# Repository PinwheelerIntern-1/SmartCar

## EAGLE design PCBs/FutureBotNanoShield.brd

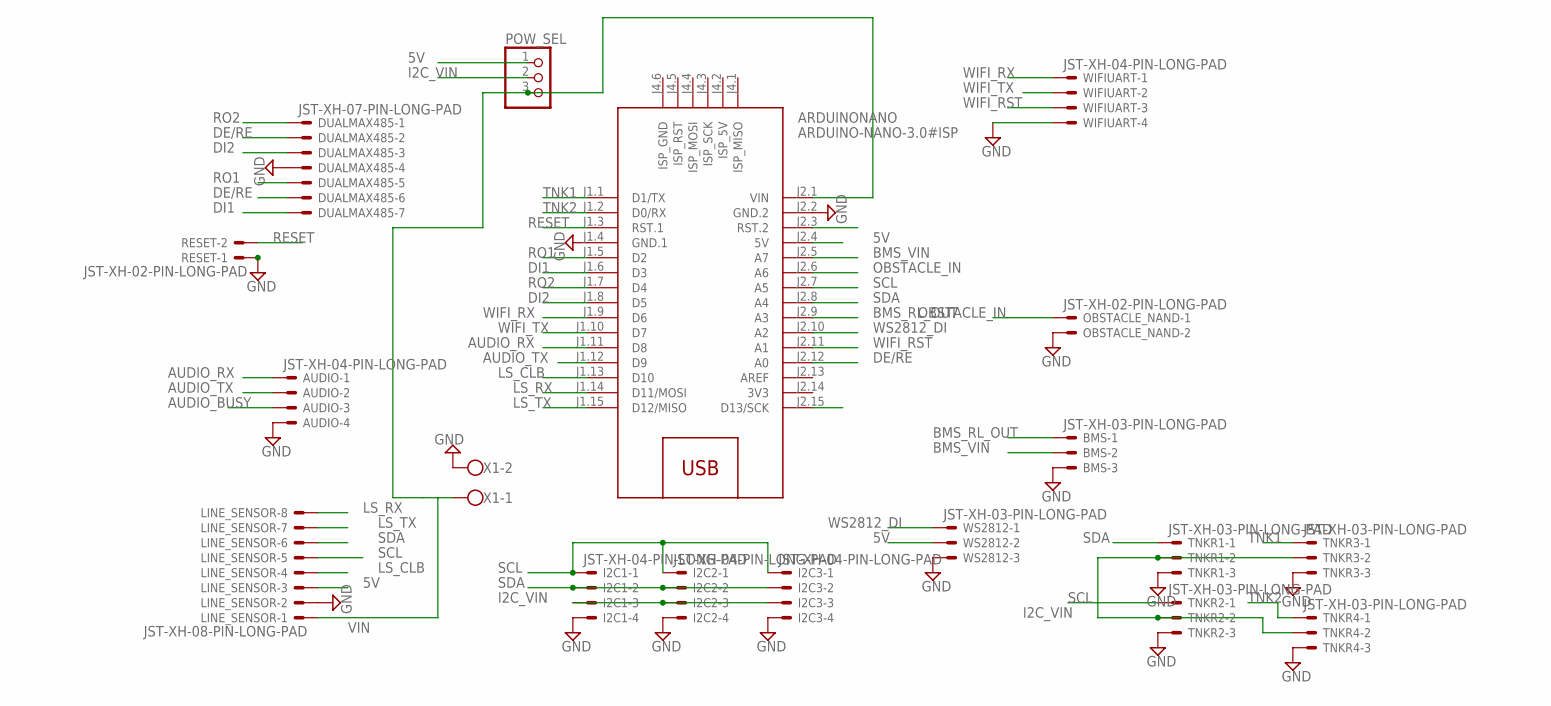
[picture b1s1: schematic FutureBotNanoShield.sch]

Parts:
ARDUINONANO: ARDUINO-NANO-3.0#ISP
AUDIO: JST-XH-04-PIN-LONG-PAD; JST-XH-04-PACKAGE-LONG-PAD
BMS: JST-XH-03-PIN-LONG-PAD; JST-XH-03-PACKAGE-LONG-PAD
DUALMAX485: JST-XH-07-PIN-LONG-PAD; JST-XH-07-PACKAGE-LONG-PAD
I2C1, I2C2, I2C3: JST-XH-04-PIN-LONG-PAD; JST-XH-04-PACKAGE-LONG-PAD
LINE_SENSOR: JST-XH-08-PIN-LONG-PAD; JST-XH-08-PACKAGE-LONG-PAD
OBSTACLE_NAND: JST-XH-02-PIN-LONG-PAD; JST-XH-02-PACKAGE-LONG-PAD
POW_SEL: PINHD-1X3; 1X03
RESET: JST-XH-02-PIN-LONG-PAD; JST-XH-02-PACKAGE-LONG-PAD
TNKR1, TNKR2, TNKR3, TNKR4: JST-XH-03-PIN-LONG-PAD; JST-XH-03-PACKAGE-LONG-PAD
WIFIUART: JST-XH-04-PIN-LONG-PAD; JST-XH-04-PACKAGE-LONG-PAD
WS2812: JST-XH-03-PIN-LONG-PAD; JST-XH-03-PACKAGE-LONG-PAD
X1: W237-102

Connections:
3V3: ARDUINONANO.J2.14 (3V3)
5V: ARDUINONANO.J2.4 (5V), LINE_SENSOR.3, POW_SEL.1, WS2812.2
AUDIO_BUSY: AUDIO.3
AUDIO_RX: ARDUINONANO.J1.11 (D8), AUDIO.1
AUDIO_TX: ARDUINONANO.J1.12 (D9), AUDIO.2
BMS_RL_OUT: ARDUINONANO.J2.9 (A3), BMS.1
BMS_VIN: ARDUINONANO.J2.5 (A7), BMS.2
DE/RE: ARDUINONANO.J2.12 (A0), DUALMAX485.2, DUALMAX485.6
DI1: ARDUINONANO.J1.6 (D3), DUALMAX485.7
DI2: ARDUINONANO.J1.8 (D5), DUALMAX485.3
GND: ARDUINONANO.J1.4 (GND.1), ARDUINONANO.J2.2 (GND.2), AUDIO.4, BMS.3, DUALMAX485.4, I2C1.4, I2C2.4, I2C3.4, LINE_SENSOR.2, OBSTACLE_NAND.2, RESET.1, TNKR1.3, TNKR2.3, TNKR3.3, TNKR4.3, WIFIUART.4, WS2812.3, X1.2
I2C_VIN: I2C1.3, I2C2.3, I2C3.3, POW_SEL.2, TNKR1.2, TNKR2.2, TNKR3.2, TNKR4.2
LS_CLB: ARDUINONANO.J1.13 (D10), LINE_SENSOR.4
LS_RX: ARDUINONANO.J1.14 (D11/MOSI), LINE_SENSOR.8
LS_TX: ARDUINONANO.J1.15 (D12/MISO), LINE_SENSOR.7
OBSTACLE_IN: ARDUINONANO.J2.6 (A6), OBSTACLE_NAND.1
RESET: ARDUINONANO.J1.3 (RST.1), RESET.2
RO1: ARDUINONANO.J1.5 (D2), DUALMAX485.5
RO2: ARDUINONANO.J1.7 (D4), DUALMAX485.1
SCL: ARDUINONANO.J2.7 (A5), I2C1.1, I2C2.1, I2C3.1, LINE_SENSOR.5, TNKR2.1
SDA: ARDUINONANO.J2.8 (A4), I2C1.2, I2C2.2, I2C3.2, LINE_SENSOR.6, TNKR1.1
TNK1: ARDUINONANO.J1.1 (D1/TX), TNKR3.1
TNK2: ARDUINONANO.J1.2 (D0/RX), TNKR4.1
VIN: ARDUINONANO.J2.1 (VIN), LINE_SENSOR.1, POW_SEL.3, X1.1
WIFI_RST: ARDUINONANO.J2.11 (A1), WIFIUART.3
WIFI_RX: ARDUINONANO.J1.9 (D6), WIFIUART.1
WIFI_TX: ARDUINONANO.J1.10 (D7), WIFIUART.2
WS2812_DI: ARDUINONANO.J2.10 (A2), WS2812.1

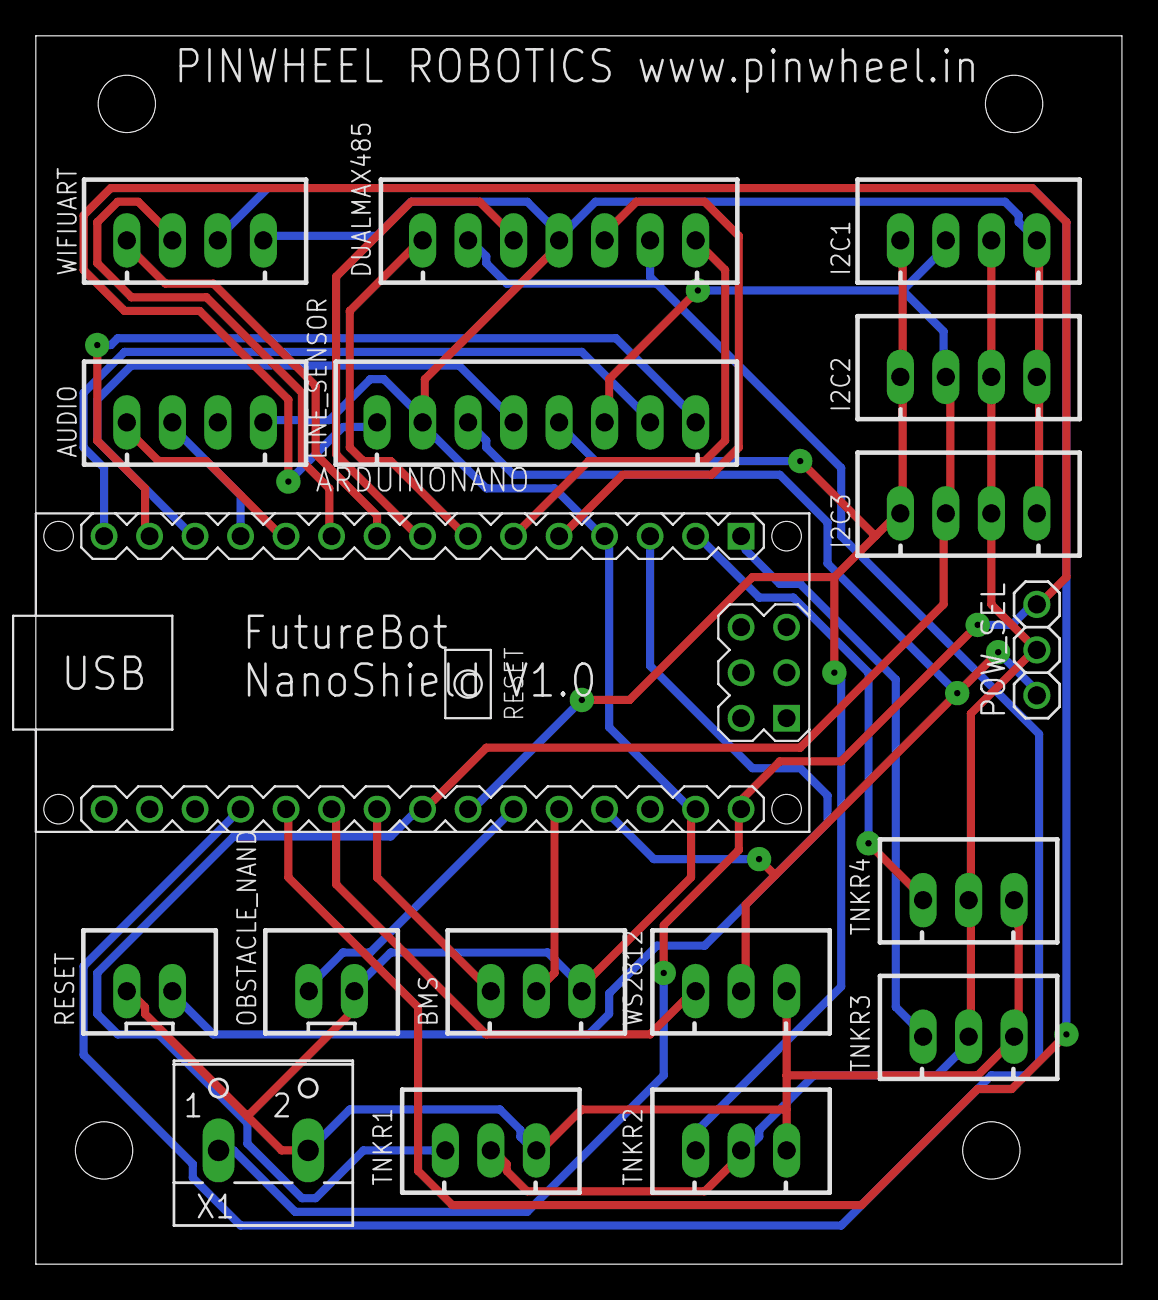
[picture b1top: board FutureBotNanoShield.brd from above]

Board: 2 copper layers, 60.6 x 68.6 mm, 18 parts (0 on the bottom side), 26 nets.

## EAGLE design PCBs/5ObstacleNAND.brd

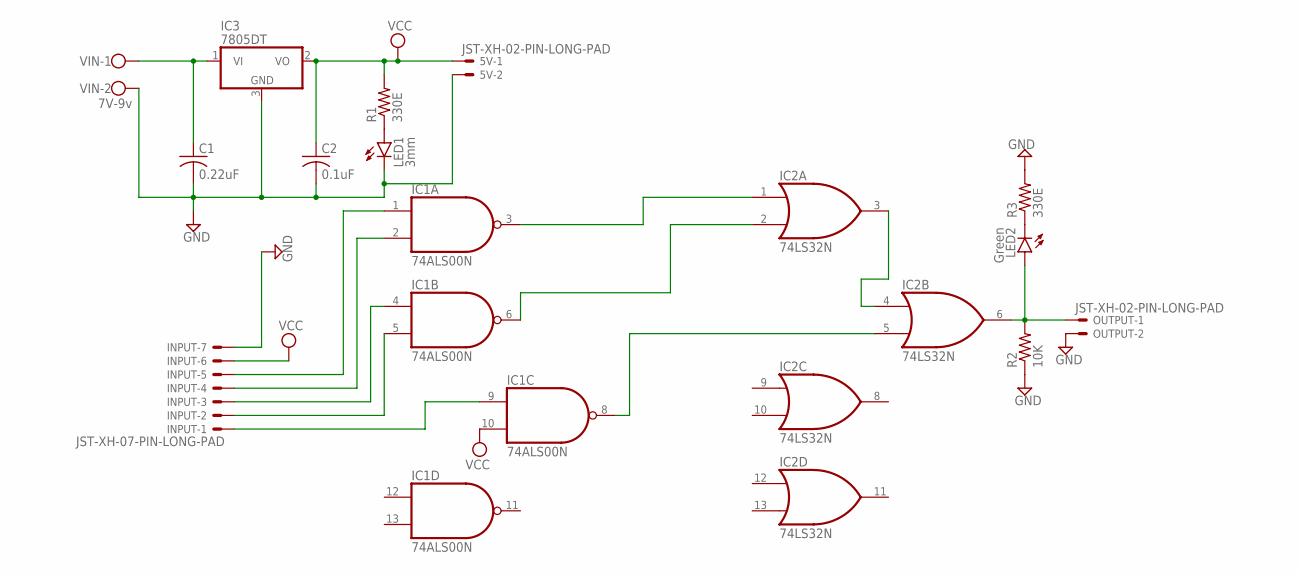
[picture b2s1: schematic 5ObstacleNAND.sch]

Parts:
5V: JST-XH-02-PIN-LONG-PAD; JST-XH-02-PACKAGE-LONG-PAD
C1: 0.22uF; C0805
C2: 0.1uF; C0805
IC1: 74ALS00N; DIL14
IC2: 74LS32N; DIL14
IC3: 7805DT; TO252
INPUT: JST-XH-07-PIN-LONG-PAD; JST-XH-07-PACKAGE-LONG-PAD
LED1: 3mm; SML0805
LED2: Green; SML0805
OUTPUT: JST-XH-02-PIN-LONG-PAD; JST-XH-02-PACKAGE-LONG-PAD
R1, R3: 330E; R0805
R2: 10K; R0805
VIN: 7V-9v; W237-102

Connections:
GND: 5V.2, C1.2, C2.2, IC1.7 (GND), IC2.7 (GND), IC3.3 (GND), INPUT.7, LED1.C, OUTPUT.2, R2.1, R3.2, VIN.2
unnamed: IC1.1 (I0), INPUT.5
unnamed: IC1.2 (I1), INPUT.4
unnamed: IC1.4 (I0), INPUT.3
unnamed: IC1.5 (I1), INPUT.2
unnamed: IC1.9 (I0), INPUT.1
unnamed: IC1.3 (O), IC2.1 (I0)
unnamed: IC1.6 (O), IC2.2 (I1)
unnamed: IC2.3 (O), IC2.4 (I0)
unnamed: IC1.8 (O), IC2.5 (I1)
unnamed: IC2.6 (O), LED2.A, OUTPUT.1, R2.2
unnamed: LED2.C, R3.1
unnamed: LED1.A, R1.1
unnamed: C1.1, IC3.1 (VI), VIN.1
VCC: 5V.1, C2.1, IC1.10 (I1), IC1.14 (VCC), IC2.14 (VCC), IC3.2 (VO), INPUT.6, R1.2

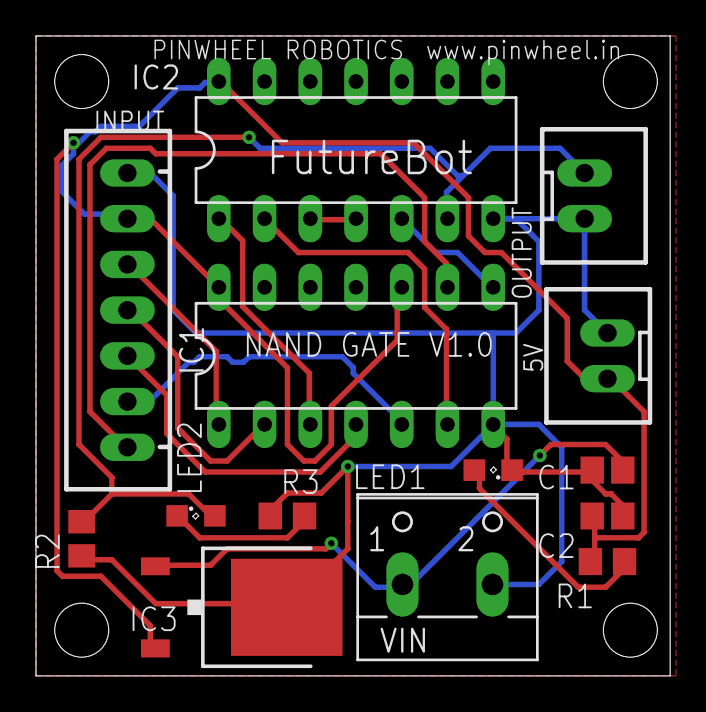
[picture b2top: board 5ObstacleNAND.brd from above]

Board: 2 copper layers, 35.2 x 35.6 mm, 14 parts (0 on the bottom side), 15 nets.

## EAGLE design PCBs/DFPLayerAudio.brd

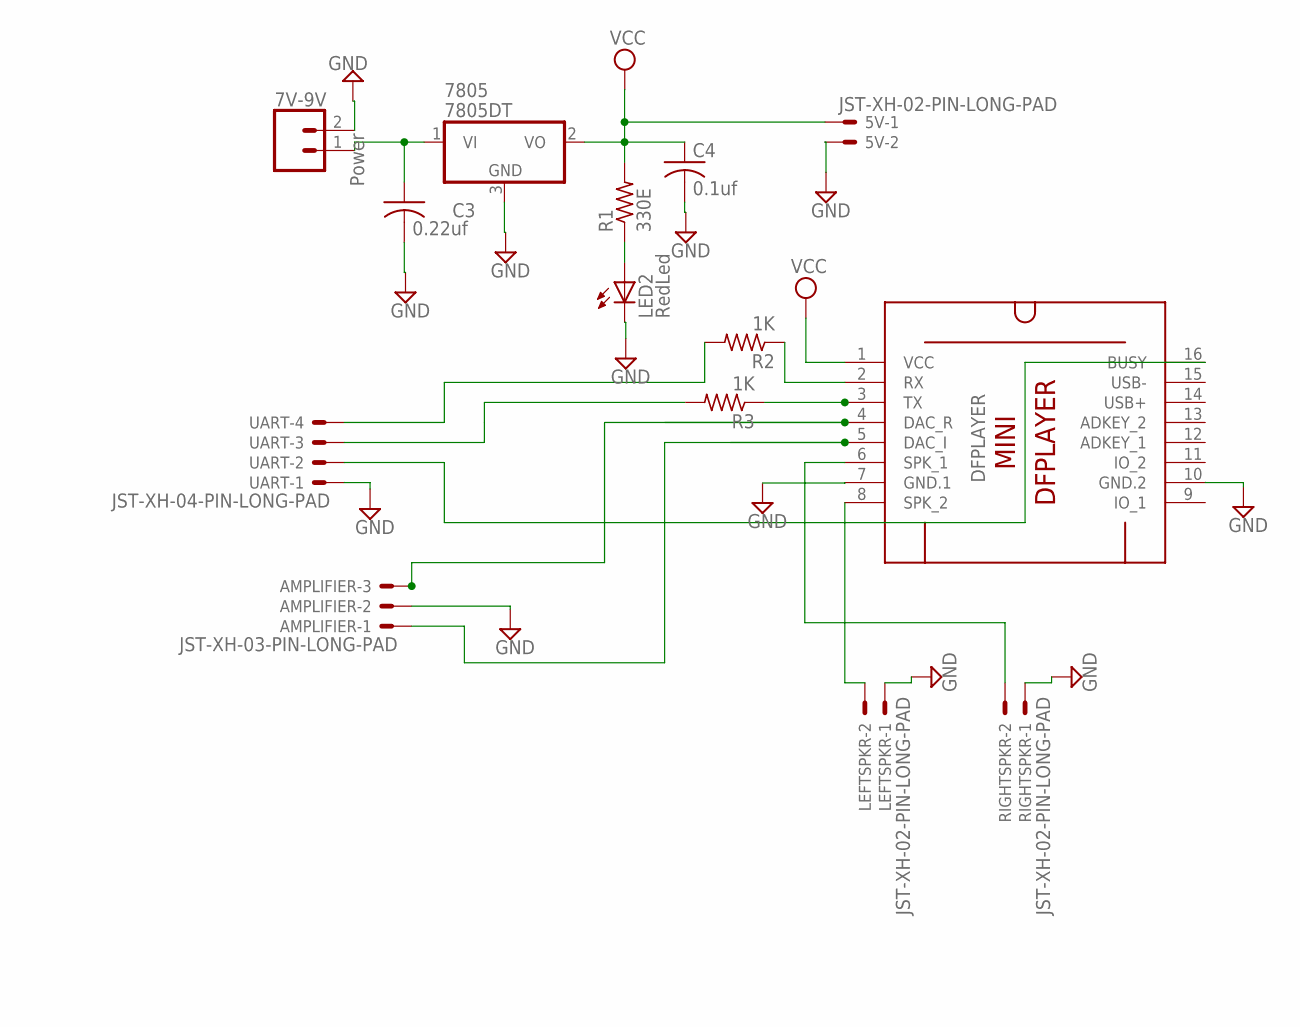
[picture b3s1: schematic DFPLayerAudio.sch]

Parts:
5V: JST-XH-02-PIN-LONG-PAD; JST-XH-02-PACKAGE-LONG-PAD
7V-9V: Power; SCREWTERMINAL-5MM-2
7805: 7805DT; TO252
AMPLIFIER: JST-XH-03-PIN-LONG-PAD; JST-XH-03-PACKAGE-LONG-PAD
C3: 0.22uf; C0805K
C4: 0.1uf; C0805K
DFPLAYER: DFPLAYER-MINI-MODULE
LED2: RedLed; CHIPLED_0805
LEFTSPKR: JST-XH-02-PIN-LONG-PAD; JST-XH-02-PACKAGE-LONG-PAD
R1: 330E; M0805
R2, R3: 1K; M0805
RIGHTSPKR: JST-XH-02-PIN-LONG-PAD; JST-XH-02-PACKAGE-LONG-PAD
UART: JST-XH-04-PIN-LONG-PAD; JST-XH-04-PACKAGE-LONG-PAD

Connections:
GND: 5V.2, 7V-9V.2, 7805.3 (GND), AMPLIFIER.2, C3.2, C4.2, DFPLAYER.7 (GND.1), DFPLAYER.10 (GND.2), LED2.C, LEFTSPKR.1, RIGHTSPKR.1, UART.1
unnamed: AMPLIFIER.3, DFPLAYER.4 (DAC_R)
unnamed: 7V-9V.1, 7805.1 (VI), C3.1
unnamed: DFPLAYER.3 (TX), R3.1
unnamed: DFPLAYER.2 (RX), R2.1
unnamed: DFPLAYER.16 (BUSY), UART.2
unnamed: R3.2, UART.3
unnamed: R2.2, UART.4
unnamed: DFPLAYER.8 (SPK_2), LEFTSPKR.2
unnamed: AMPLIFIER.1, DFPLAYER.5 (DAC_I)
unnamed: LED2.A, R1.1
unnamed: DFPLAYER.6 (SPK_1), RIGHTSPKR.2
VCC: 5V.1, 7805.2 (VO), C4.1, DFPLAYER.1 (VCC), R1.2

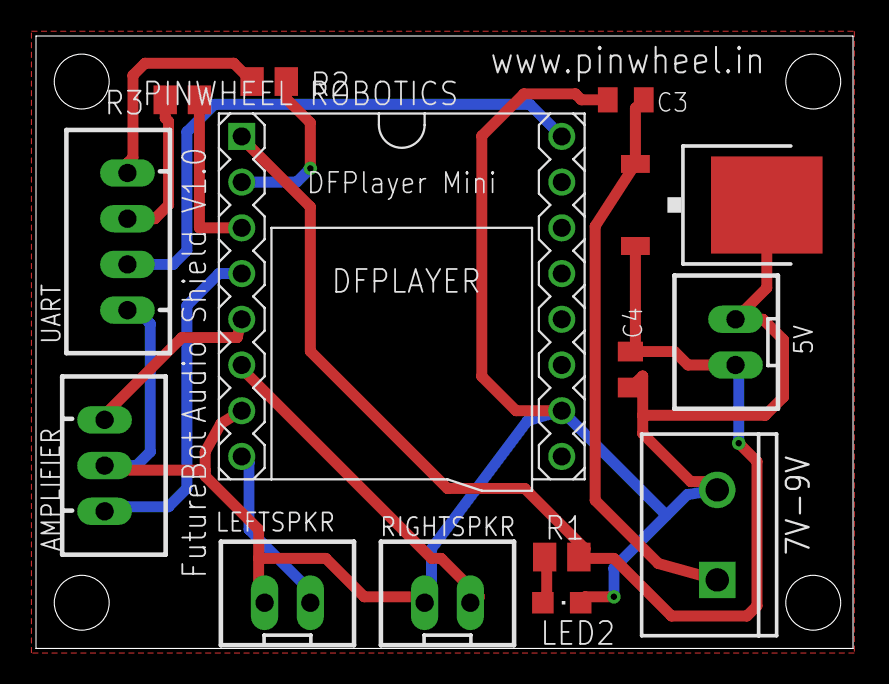
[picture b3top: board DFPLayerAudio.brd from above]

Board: 2 copper layers, 45.4 x 34.0 mm, 14 parts (0 on the bottom side), 13 nets.

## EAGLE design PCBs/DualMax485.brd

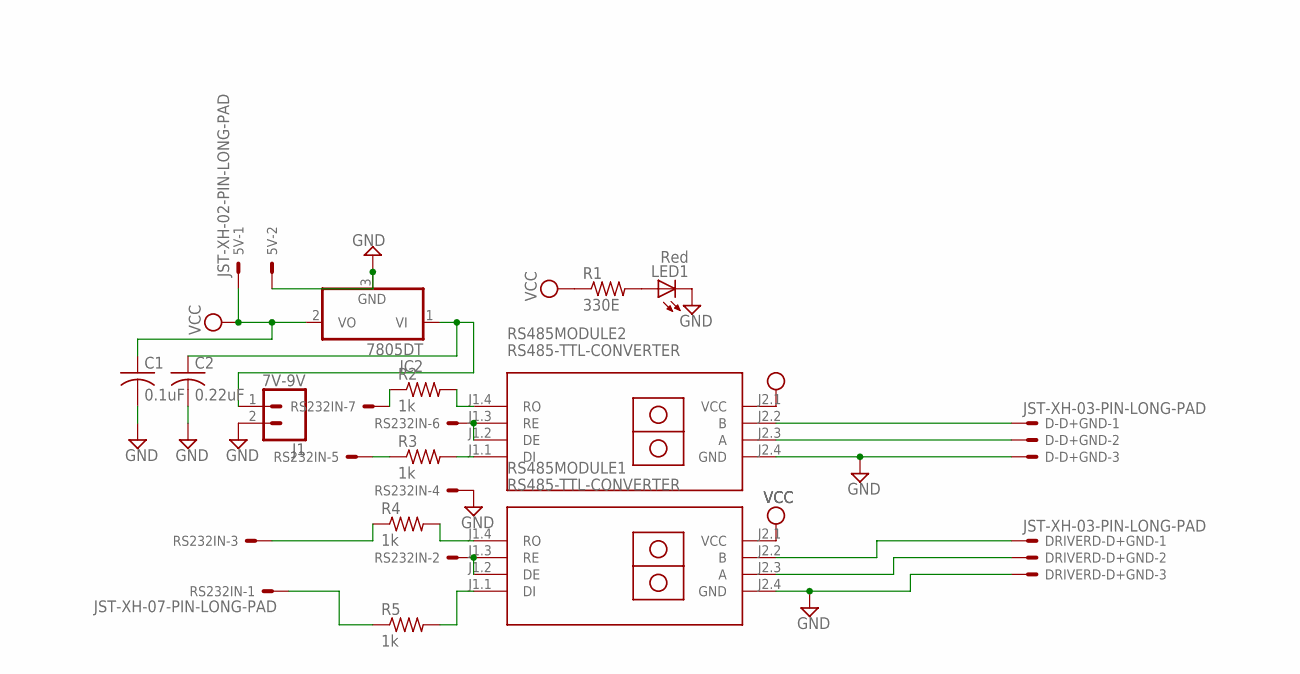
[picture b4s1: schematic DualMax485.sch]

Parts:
5V: JST-XH-02-PIN-LONG-PAD; JST-XH-02-PACKAGE-LONG-PAD
C1: 0.1uF; C0805
C2: 0.22uF; C0805
D-D+GND: JST-XH-03-PIN-LONG-PAD; JST-XH-03-PACKAGE-LONG-PAD
DRIVERD-D+GND: JST-XH-03-PIN-LONG-PAD; JST-XH-03-PACKAGE-LONG-PAD
IC2: 7805DT; TO252
J1: 7V-9V; SCREWTERMINAL-5MM-2
LED1: Red; CHIPLED_0805
R1: 330E; M0805
R2, R3, R4, R5: 1k; M0805
RS232IN: JST-XH-07-PIN-LONG-PAD; JST-XH-07-PACKAGE-LONG-PAD
RS485MODULE1, RS485MODULE2: RS485-TTL-CONVERTER

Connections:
GND: 5V.2, C1.2, C2.2, D-D+GND.3, DRIVERD-D+GND.3, IC2.3 (GND), J1.2, LED1.C, RS232IN.4, RS485MODULE1.J2.4 (GND), RS485MODULE2.J2.4 (GND)
unnamed: RS232IN.6, RS485MODULE2.J1.2 (DE), RS485MODULE2.J1.3 (RE)
unnamed: R3.2, RS485MODULE2.J1.1 (DI)
unnamed: R2.2, RS485MODULE2.J1.4 (RO)
unnamed: D-D+GND.1, RS485MODULE2.J2.2 (B)
unnamed: R3.1, RS232IN.5
unnamed: D-D+GND.2, RS485MODULE2.J2.3 (A)
unnamed: RS232IN.2, RS485MODULE1.J1.2 (DE), RS485MODULE1.J1.3 (RE)
unnamed: R5.1, RS232IN.1
unnamed: LED1.A, R1.2
unnamed: R4.1, RS232IN.3
unnamed: R2.1, RS232IN.7
unnamed: DRIVERD-D+GND.1, RS485MODULE1.J2.2 (B)
unnamed: DRIVERD-D+GND.2, RS485MODULE1.J2.3 (A)
unnamed: R4.2, RS485MODULE1.J1.4 (RO)
unnamed: R5.2, RS485MODULE1.J1.1 (DI)
unnamed: C2.1, IC2.1 (VI), J1.1
VCC: 5V.1, C1.1, IC2.2 (VO), R1.1, RS485MODULE1.J2.1 (VCC), RS485MODULE2.J2.1 (VCC)

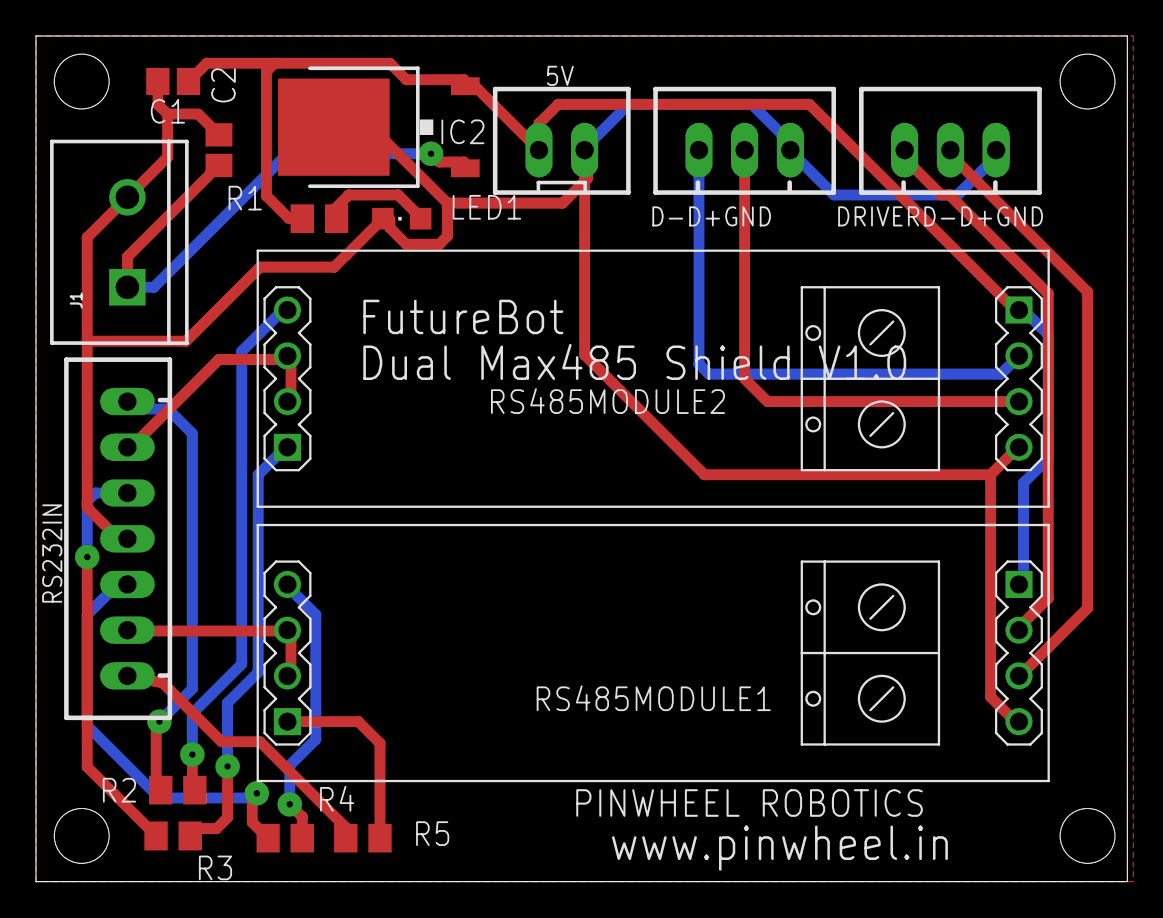
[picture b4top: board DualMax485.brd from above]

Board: 2 copper layers, 60.6 x 47.0 mm, 16 parts (0 on the bottom side), 18 nets.

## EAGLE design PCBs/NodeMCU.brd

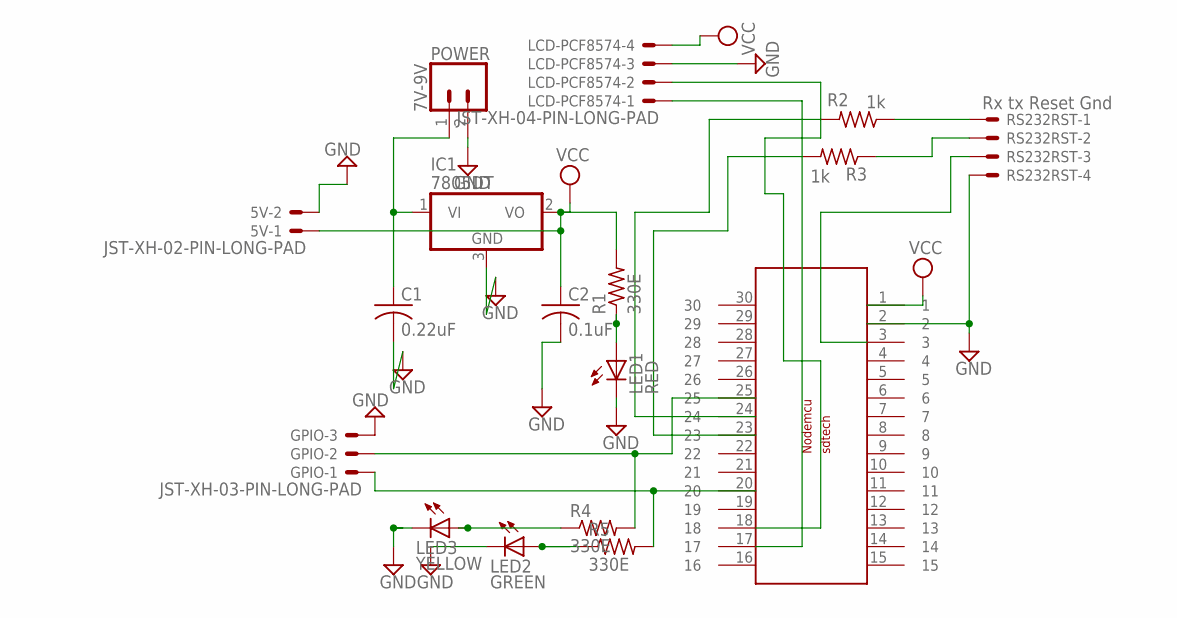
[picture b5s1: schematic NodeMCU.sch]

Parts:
5V: JST-XH-02-PIN-LONG-PAD; JST-XH-02-PACKAGE-LONG-PAD
C1: 0.22uF; C0805K
C2: 0.1uF; C0805K
GPIO: JST-XH-03-PIN-LONG-PAD; JST-XH-03-PACKAGE-LONG-PAD
IC1: 7805DT; TO252
LCD-PCF8574: JST-XH-04-PIN-LONG-PAD; JST-XH-04-PACKAGE-LONG-PAD
LED1: RED; CHIPLED_0805
LED2: GREEN; CHIPLED_0805
LED3: YELLOW; CHIPLED_0805
POWER: 7V-9V; SCREWTERMINAL-5MM-2
R1, R4, R5: 330E; M0805
R2, R3: 1k; M0805
RS232RST: Rx tx Reset Gnd; JST-XH-04-PACKAGE-LONG-PAD
U$2: NodeMCU-ESP12E; NODEMCUESP8266

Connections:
GND: 5V.2, C1.2, C2.2, GPIO.3, IC1.3 (GND), LCD-PCF8574.3, LED1.C, LED2.C, LED3.C, POWER.2, RS232RST.4, U$2.2
unnamed: LED1.A, R1.1
unnamed: LCD-PCF8574.2, U$2.18
unnamed: LED3.A, R4.1
unnamed: LED2.A, R5.1
unnamed: R2.1, RS232RST.1
unnamed: R2.2, U$2.24
unnamed: LCD-PCF8574.1, U$2.17
unnamed: R3.2, U$2.23
unnamed: C1.1, IC1.1 (VI), POWER.1
unnamed: R3.1, RS232RST.2
unnamed: RS232RST.3, U$2.3
unnamed: GPIO.2, R4.2, U$2.25
unnamed: GPIO.1, R5.2, U$2.20
VCC: 5V.1, C2.1, IC1.2 (VO), LCD-PCF8574.4, R1.2, U$2.1

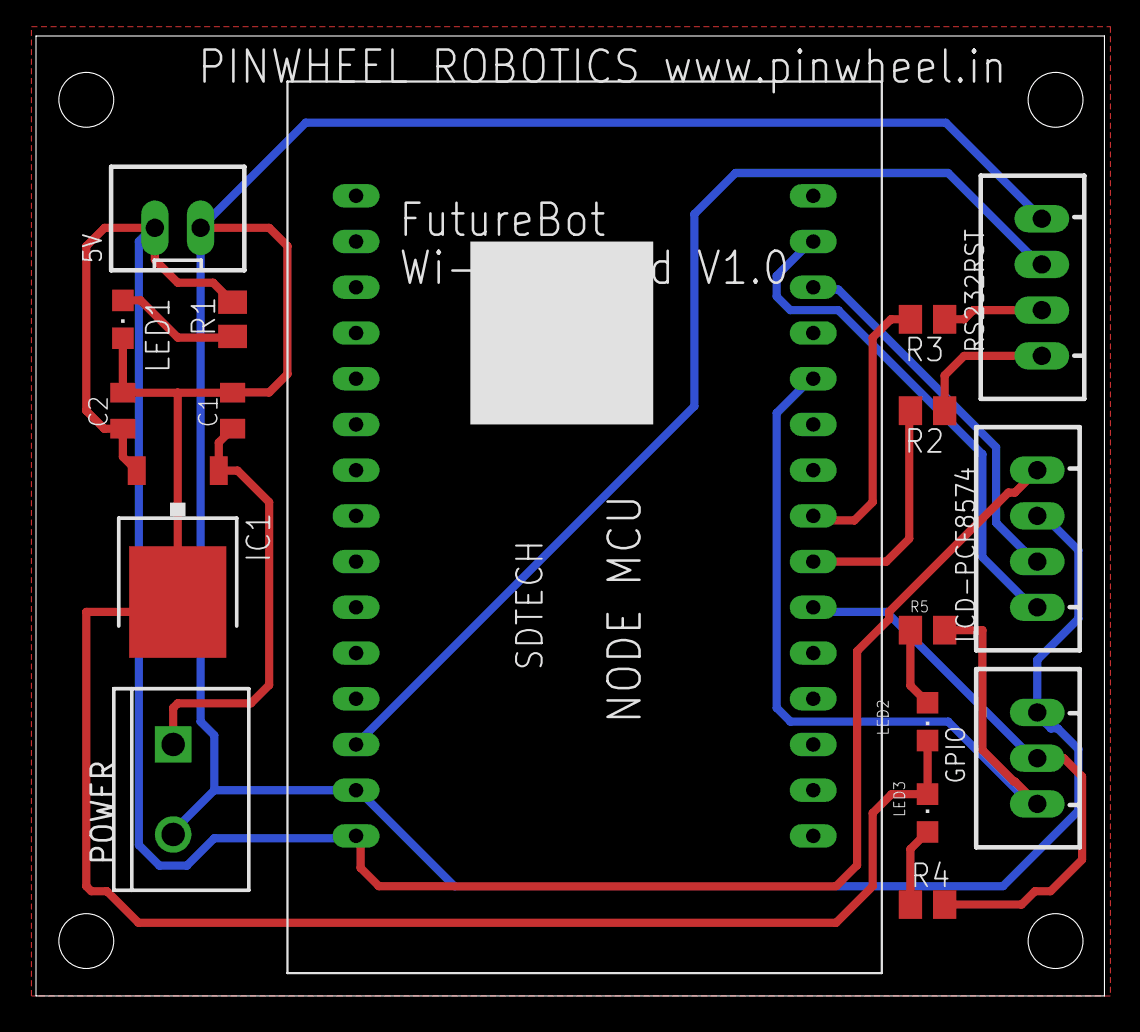
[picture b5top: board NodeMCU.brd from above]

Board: 2 copper layers, 59.4 x 53.3 mm, 17 parts (0 on the bottom side), 15 nets.

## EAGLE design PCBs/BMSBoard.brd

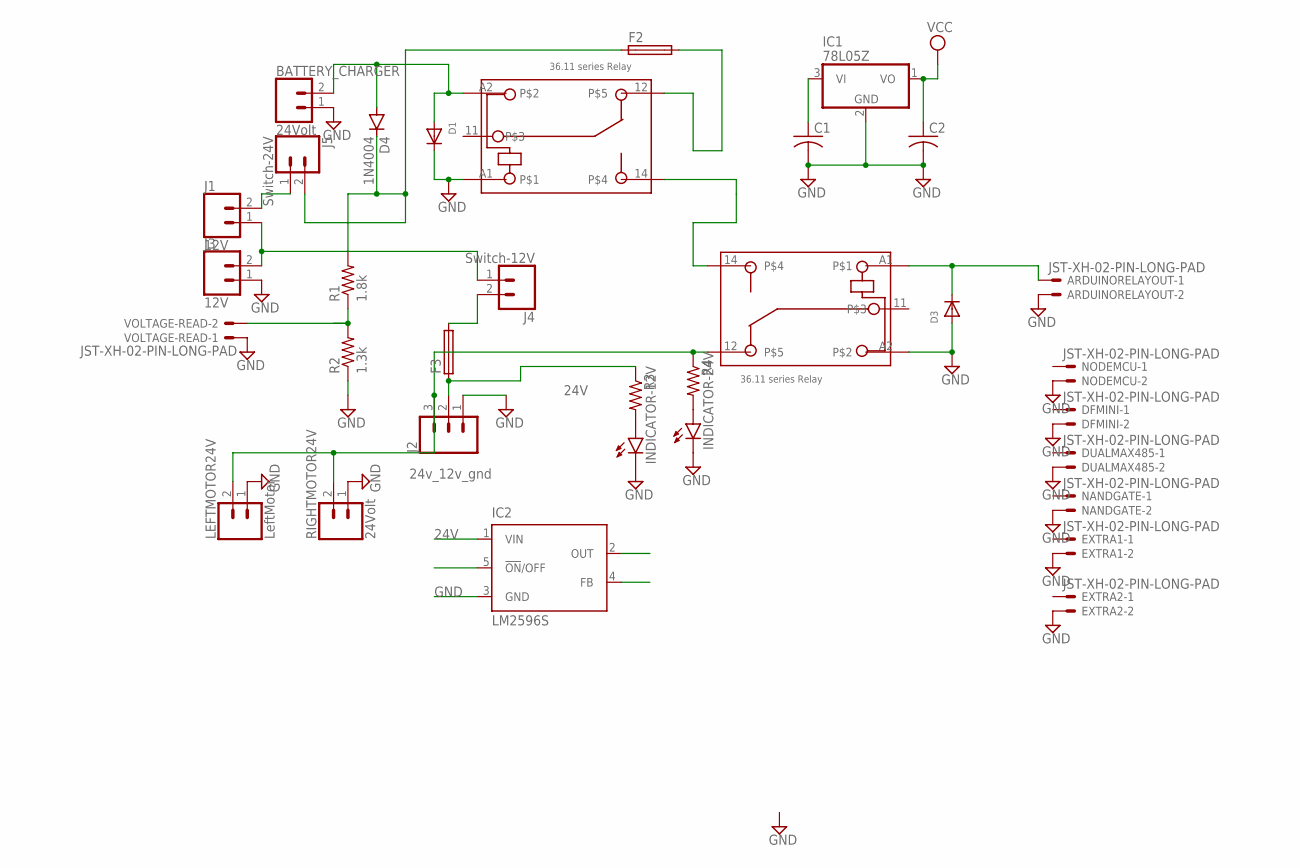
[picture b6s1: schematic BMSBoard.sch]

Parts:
ARDUINORELAYOUT: JST-XH-02-PIN-LONG-PAD; JST-XH-02-PACKAGE-LONG-PAD
BATTERY_CHARGER: 24Volt; SCREWTERMINAL-3.5MM-2
BMSRELAY: 36.11
C1, C2: C-US025-024X044; C025-024X044
CHARGERRELAY: 36.11
D1, D3: DIODEDO-1N4148; DO-1N4148
D4: 1N4004; DO41-10
DFMINI: JST-XH-02-PIN-LONG-PAD; JST-XH-02-PACKAGE-LONG-PAD
DUALMAX485: JST-XH-02-PIN-LONG-PAD; JST-XH-02-PACKAGE-LONG-PAD
EXTRA1, EXTRA2: JST-XH-02-PIN-LONG-PAD; JST-XH-02-PACKAGE-LONG-PAD
F2, F3: 19560
IC1: 78L05Z; TO92
IC2: LM2596S; TO263-5
INDICATOR-12V, INDICATOR-24V: LED; SMARTLED-TTW
J1, J3: 12V; SCREWTERMINAL-3.5MM-2
J2: 24v_12v_gnd; SCREWTERMINAL-5MM-3
J4: Switch-12V; SCREWTERMINAL-3.5MM-2
J5: Switch-24V; SCREWTERMINAL-3.5MM-2
LEFTMOTOR24V: LeftMotor; SCREWTERMINAL-3.5MM-2
NANDGATE: JST-XH-02-PIN-LONG-PAD; JST-XH-02-PACKAGE-LONG-PAD
NODEMCU: JST-XH-02-PIN-LONG-PAD; JST-XH-02-PACKAGE-LONG-PAD
R1: 1.8k; 0204/7
R2: 1.3k; 0204/7
R3, R4: R-US_0204/2V; 0204V
RIGHTMOTOR24V: 24Volt; SCREWTERMINAL-3.5MM-2
VOLTAGE-READ: JST-XH-02-PIN-LONG-PAD; JST-XH-02-PACKAGE-LONG-PAD

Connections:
24V: F3.1, IC2.1 (VIN), J2.2, R3.1
GND: ARDUINORELAYOUT.2, BATTERY_CHARGER.1, BMSRELAY.A2, C1.2, C2.2, CHARGERRELAY.A1, D1.C, D3.A, DFMINI.2, DUALMAX485.2, EXTRA1.2, EXTRA2.2, IC1.2 (GND), IC2.3 (GND), INDICATOR-12V.C@1 (C), INDICATOR-24V.C@1 (C), J2.1, J3.1, LEFTMOTOR24V.1, NANDGATE.2, NODEMCU.2, R2.1, RIGHTMOTOR24V.1, VOLTAGE-READ.1
unnamed: R1.1, R2.2, VOLTAGE-READ.2
unnamed: BATTERY_CHARGER.2, CHARGERRELAY.A2, D1.A, D4.A
unnamed: CHARGERRELAY.12, F2.2
unnamed: ARDUINORELAYOUT.1, BMSRELAY.A1, D3.C
unnamed: D4.C, F2.1, J5.2, R1.2
unnamed: BMSRELAY.14, CHARGERRELAY.14
unnamed: BMSRELAY.12, J2.3, LEFTMOTOR24V.2, R4.1, RIGHTMOTOR24V.2
unnamed: J1.1, J3.2, J4.1
unnamed: C1.1, IC1.3 (VI)
unnamed: J1.2, J5.1
unnamed: F3.2, J4.2
unnamed: INDICATOR-24V.A@1 (A), R4.2
unnamed: INDICATOR-12V.A@1 (A), R3.2
VCC: C2.1, IC1.1 (VO)

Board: 2 copper layers, 33 parts (0 on the bottom side), 16 nets, no tracks yet.

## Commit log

2021-11-23 InitialDesign and Code
2021-11-23 Updated with Calibrate and Line Mode
2021-11-23 adding libraries that are used in the code.
2021-11-23 adding test code for Ring LED based on WS2812
2021-11-23 Adding Audio file to be stored in SD Card
2021-11-23 daTD N NMB
2021-11-24 Adding BMS Schematic
2021-11-25 Adding Test Code with All Module Integrated
2021-11-25 Removing ModBus Library
2021-11-25 Adding Modbus Library
2021-11-25 adding properties file
2021-11-25 updaqted
2021-11-25 Audio For car updated.
2021-11-25 RenamedAudioSorted
2021-11-25 Added Lookup Table
2021-11-25 upadted with audio file and some bug fixes
2021-11-26 updated audio with 200msec delay.
2021-11-26 corel draw design added
2021-11-26 mounting holes added
2021-11-26 Updated code to play audio file based on number
2021-11-26 fixed bug related to audio play
2021-11-27 updated with mounting holes
2021-11-28 cvfcvb
2021-11-29 TX and Rx pin updated with resistor
2021-11-29 resistors added to max485
2021-11-29 updated board
2021-11-29 board updated
2021-11-29 added something
2021-11-29 updated something
2021-11-30 Nand Gate Board updated
2021-11-30 audio board updated
2021-11-30 naming part of audio board updated
2021-11-30 updated gerber and corrected few things
2021-11-30 Changed Pin number in future if we connect LCD module to it.
2021-12-01 added connector for Vin and 5V
2021-12-01 updated nand gate amd nodmcu
2021-12-01 Adding Test code to be used for testing future bot with line sensor and follow line.
2021-12-01 Generated Gerber after Ratsnest
2021-12-03 Adding the Nano Shield for Future Bot
2021-12-03 naming convention

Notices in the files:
parts and their libraries:
SparkFun-Connectors: Licensing: Creative Commons ShareAlike 4.0 International - https://creativecommons.org/licenses/by-sa/4.0
diy-modules: Released under the Creative Commons Attribution 4.0 International License: http://creativecommons.org/licenses/by/4.0
